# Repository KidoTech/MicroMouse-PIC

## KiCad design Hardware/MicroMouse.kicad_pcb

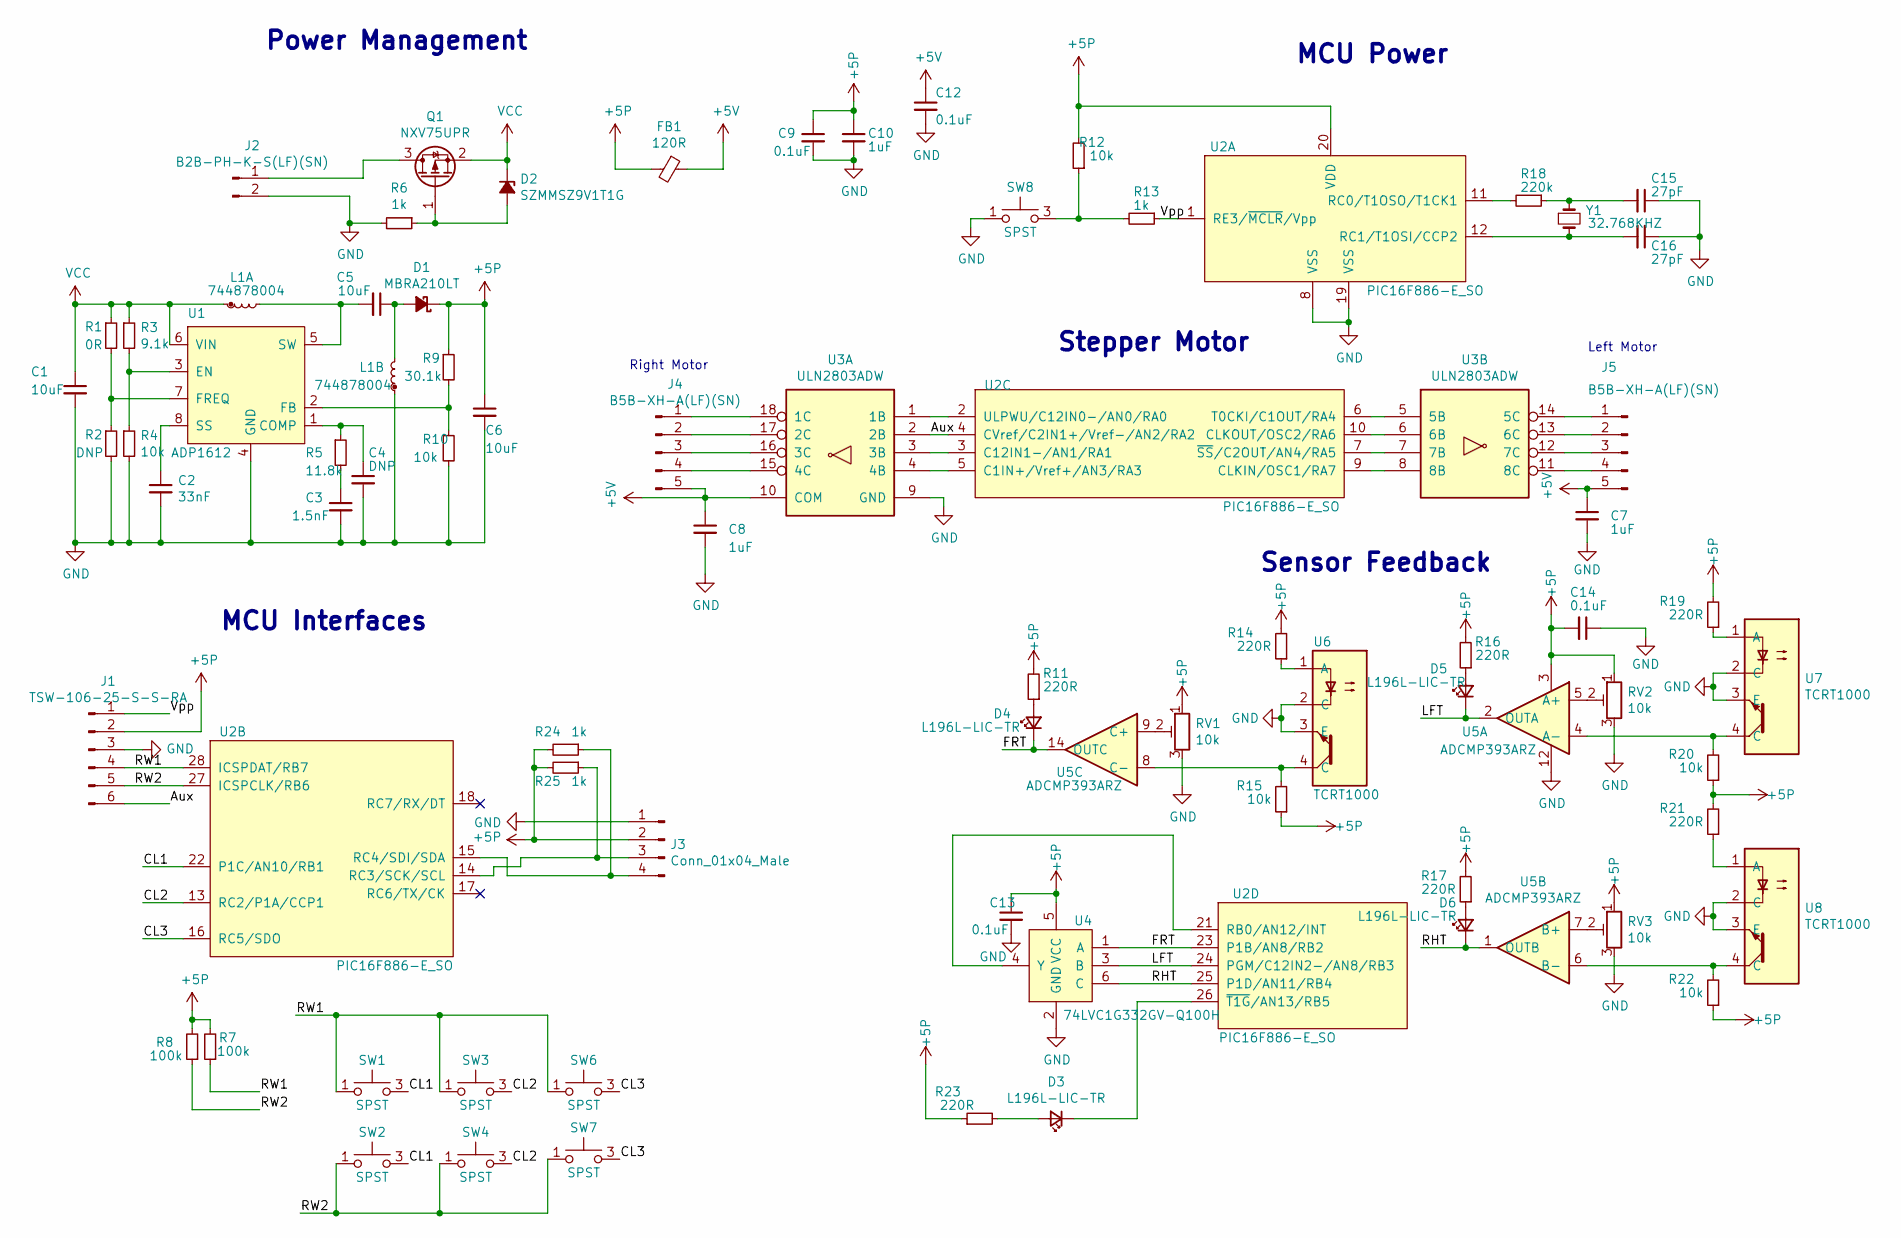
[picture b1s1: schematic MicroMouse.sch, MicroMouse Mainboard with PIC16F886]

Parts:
C1, C5, C6: 10uF; CAP0805
C2: 33nF; CAP0603
C3: 1.5nF; CAP0603
C4: DNP; CAP0603
C7, C8, C10: 1uF; CAP0603
C9, C12, C13, C14: 0.1uF; CAP0603
C15, C16: 27pF; CAP0603
D1: MBRA210LT; MBRA210-SMA
D2: SZMMSZ9V1T1G; SZMMSZ9-SOD123
D3, D4, D5, D6: L196L-LIC-TR; LTST-C170-0805
FB1: 120R; FER0603
J1: TSW-106-25-S-S-RA; THRU-254-RHT-6P
J2: B2B-PH-K-S(LF)(SN); THRU-200-STR-2P
J3: Conn_01x04_Male; THRU-254-STR-4P
J4, J5: B5B-XH-A(LF)(SN); THRU-250-STR-5P
L1: 744878004; 744878004-SMD
Q1: NXV75UPR; NXV75UPR-SOT233
R1: 0R; RES0603
R2: DNP; RES0603
R3: 9.1k; RES0603
R4, R10, R12, R15, R20, R22: 10k; RES0603
R5: 11.8k; RES0603
R6, R13, R24, R25: 1k; RES0603
R7, R8: 100k; RES0603
R9: 30.1k; RES0603
R11, R14, R16, R17, R19, R21, R23: 220R; RES0603
R18: 220k; RES0603
RV1, RV2, RV3: 10k; 3306K-THRU
SW1, SW2, SW3, SW4, SW6, SW7, SW8: SPST; PTS526-4SMD
U1: ADP1612; ADP1612-8MSOP
U2: PIC16F886-E_SO; PIC16F886-28SOIC
U3: ULN2803ADW; ULN2803A-18SO
U4: 74LVC1G332GV-Q100H; 74LVC1G332-6TSOP
U5: ADCMP393ARZ; ADCMP393-14SOIC
U6, U7, U8: TCRT1000; TCRT1000-THRU
Y1: 32.768KHZ; ECX1210-2SMD

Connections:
+5P: C6.1, C9.1, C10.1, C13.1, C14.2, D1.1 (K), FB1.2, J1.2, J3.2, R7.2, R8.2, R9.1, R11.2, R12.2, R14.2, R15.1, R16.2, R17.2, R19.2, R20.1, R21.2, R22.1, R23.1, R24.2, R25.2, RV1.1, RV2.1, RV3.1, U2.20 (VDD), U4.5 (VCC), U5.3
+5V: C7.1, C8.1, C12.1, FB1.1, J4.5, J5.5, U3.10 (COM)
/Aux: J1.6, U2.4 (CVref/C2IN1+/Vref-/AN2/RA2), U3.2 (2B)
/CL1: SW1.3 (B), SW1.4 (B), SW2.3 (B), SW2.4 (B), U2.22 (P1C/AN10/RB1)
/CL2: SW3.3 (B), SW3.4 (B), SW4.3 (B), SW4.4 (B), U2.13 (RC2/P1A/CCP1)
/CL3: SW6.3 (B), SW6.4 (B), SW7.3 (B), SW7.4 (B), U2.16 (RC5/SDO)
/FRT: D4.1 (K), U2.23 (P1B/AN8/RB2), U4.1 (A), U5.14 (OUTC)
/LFT: D5.1 (K), U2.24 (PGM/C12IN2-/AN8/RB3), U4.3 (B), U5.2 (OUTA)
/RHT: D6.1 (K), U2.25 (P1D/AN11/RB4), U4.6 (C), U5.1 (OUTB)
/RW1: J1.4, R7.1, SW1.1 (A), SW1.2 (A), SW3.1 (A), SW3.2 (A), SW6.1 (A), SW6.2 (A), U2.28 (ICSPDAT/RB7)
/RW2: J1.5, R8.1, SW2.1 (A), SW2.2 (A), SW4.1 (A), SW4.2 (A), SW7.1 (A), SW7.2 (A), U2.27 (ICSPCLK/RB6)
/Vpp: J1.1, R13.1, U2.1 (RE3/~MCLR~/Vpp)
GND: C1.2, C2.2, C3.2, C4.2, C6.2, C7.2, C8.2, C9.2, C10.2, C12.2, C13.2, C14.1, C15.1, C16.1, J1.3, J2.2, J3.1, L1.4, R2.2, R4.2, R6.2, R10.2, RV1.3, RV2.3, RV3.3, SW8.1 (A), SW8.2 (A), U1.4 (GND), U2.8 (VSS), U2.19 (VSS), U3.9 (GND), U4.2 (GND), U5.12, U6.2 (C), U6.3 (E), U7.2 (C), U7.3 (E), U8.2 (C), U8.3 (E)
unnamed: C2.1, U1.8 (SS)
unnamed: C3.1, R5.2
unnamed: C4.1, R5.1, U1.1 (COMP)
unnamed: C5.1, D1.2 (A), L1.3
unnamed: C5.2, L1.2, U1.5 (SW)
unnamed: C15.2, R18.1, Y1.1
unnamed: C16.2, U2.12 (RC1/T1OSI/CCP2), Y1.2
unnamed: D2.2 (A), Q1.1 (G), R6.1
unnamed: D3.1 (K), U2.26 (~T1G~/AN13/RB5)
unnamed: D3.2 (A), R23.2
unnamed: D4.2 (A), R11.1
unnamed: D5.2 (A), R16.1
unnamed: D6.2 (A), R17.1
unnamed: J2.1, Q1.3 (D)
unnamed: J3.3, R25.1, U2.14 (RC3/SCK/SCL)
unnamed: J3.4, R24.1, U2.15 (RC4/SDI/SDA)
unnamed: J4.1, U3.18 (1C)
unnamed: J4.2, U3.17 (2C)
unnamed: J4.3, U3.16 (3C)
unnamed: J4.4, U3.15 (4C)
unnamed: J5.1, U3.14 (5C)
unnamed: J5.2, U3.13 (6C)
unnamed: J5.3, U3.12 (7C)
unnamed: J5.4, U3.11 (8C)
unnamed: R1.2, R2.1, U1.7 (FREQ)
unnamed: R3.2, R4.1, U1.3 (EN)
unnamed: R9.2, R10.1, U1.2 (FB)
unnamed: R12.1, R13.2, SW8.3 (B), SW8.4 (B)
unnamed: R14.1, U6.1 (A)
unnamed: R15.2, U5.8 (C-), U6.4 (C)
unnamed: R18.2, U2.11 (RC0/T1OSO/T1CK1)
unnamed: R19.1, U7.1 (A)
unnamed: R20.2, U5.4 (A-), U7.4 (C)
unnamed: R21.1, U8.1 (A)
unnamed: R22.2, U5.6 (B-), U8.4 (C)
unnamed: RV1.2, U5.9 (C+)
unnamed: RV2.2, U5.5 (A+)
unnamed: RV3.2, U5.7 (B+)
unnamed: U2.2 (ULPWU/C12IN0-/AN0/RA0), U3.1 (1B)
unnamed: U2.3 (C12IN1-/AN1/RA1), U3.3 (3B)
unnamed: U2.5 (C1IN+/Vref+/AN3/RA3), U3.4 (4B)
unnamed: U2.6 (T0CKI/C1OUT/RA4), U3.5 (5B)
unnamed: U2.7 (~SS~/C2OUT/AN4/RA5), U3.7 (7B)
unnamed: U2.9 (CLKIN/OSC1/RA7), U3.8 (8B)
unnamed: U2.10 (CLKOUT/OSC2/RA6), U3.6 (6B)
unnamed: U2.21 (RB0/AN12/INT), U4.4 (Y)
VCC: C1.1, D2.1 (K), L1.1, Q1.2 (S), R1.1, R3.1, U1.6 (VIN)

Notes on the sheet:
Power Management
MCU Power
MCU Interfaces
Stepper Motor
Left Motor
Right Motor
Sensor Feedback

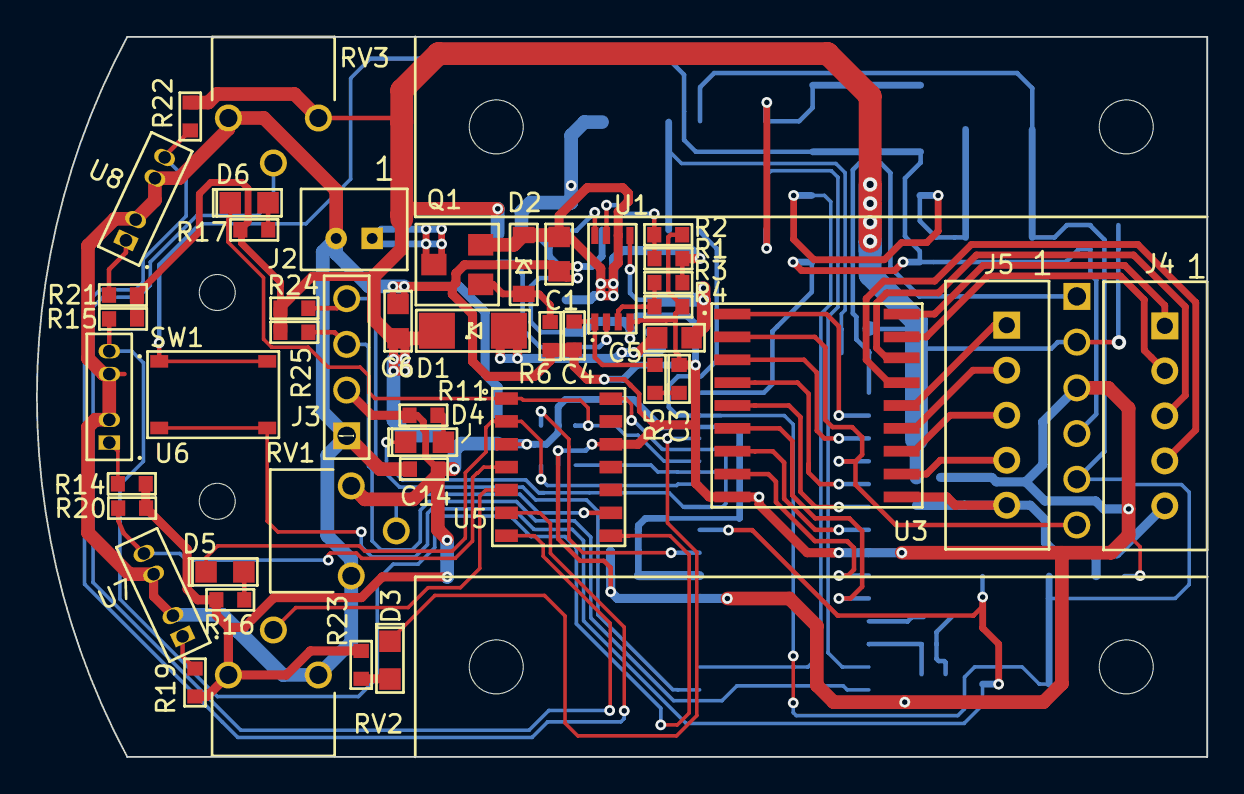
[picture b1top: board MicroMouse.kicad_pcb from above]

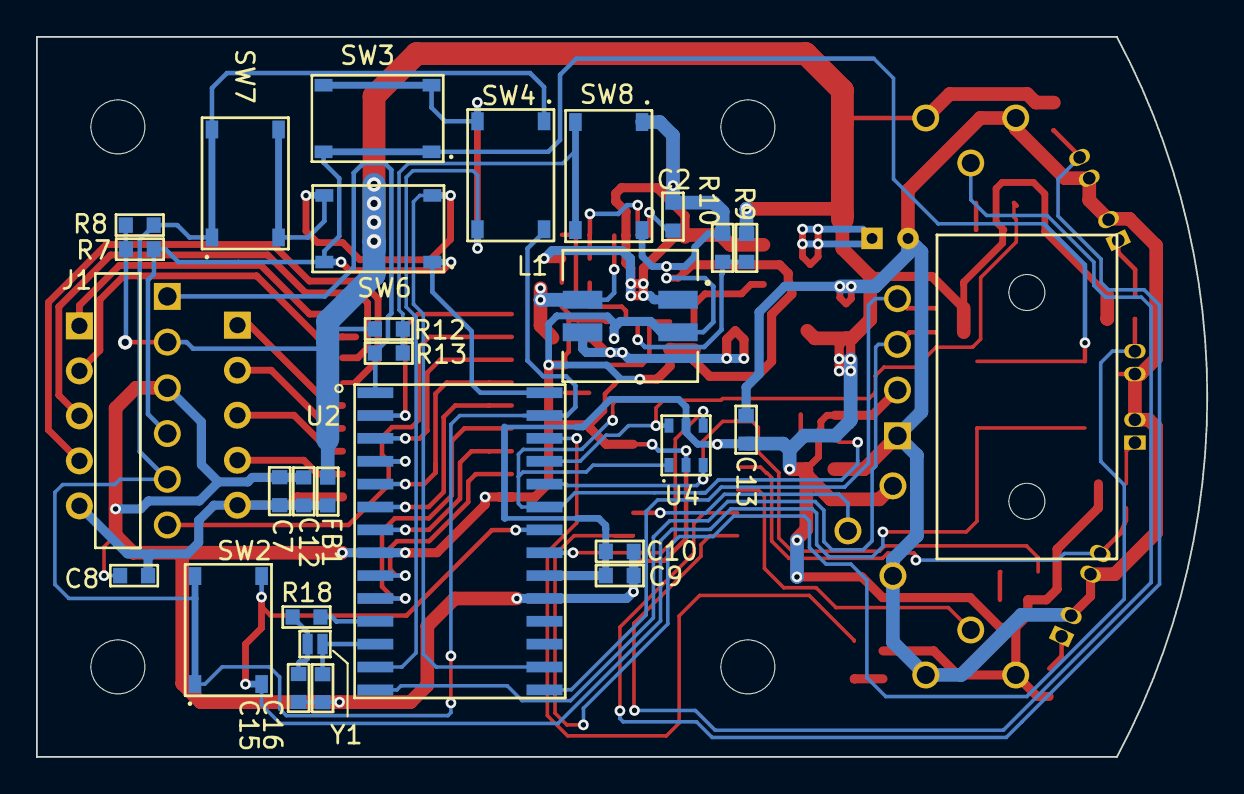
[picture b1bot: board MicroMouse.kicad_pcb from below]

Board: 2 copper layers, 65.0 x 40.0 mm, 73 parts (28 on the bottom side), 60 nets.

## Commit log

2021-04-02 Update design
2021-04-03 Create BOM
2021-04-03 Add battery holder and add matrix button
2021-04-03 Add BOM
2021-04-04 Create new foot print
2021-04-04 Add new footprint
2021-04-06 Add footprint to project
2021-04-11 Generate Schematic PDF
2021-04-11 Add LED for IR detection
2021-06-20 Update Layout
2021-06-21 Layout
2021-06-24 Layout Update
2022-01-05 Generate Gerber files
